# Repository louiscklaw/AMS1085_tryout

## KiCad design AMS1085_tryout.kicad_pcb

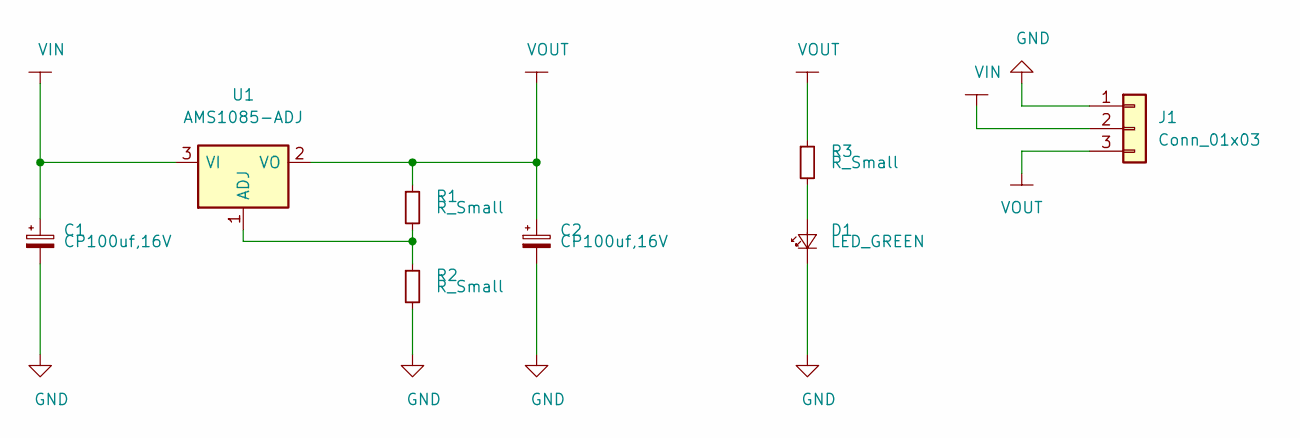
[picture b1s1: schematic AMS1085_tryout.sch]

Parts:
C1, C2: CP100uf,16V; CP_Elec_6.3x5.3
D1: LED_GREEN; LED_0805_2012Metric_Pad1.15x1.40mm_HandSolder
J1: Conn_01x03; PinHeader_1x03_P2.54mm_Vertical
R1, R2, R3: R_Small; R_1206_3216Metric_Pad1.42x1.75mm_HandSolder
U1: AMS1085-ADJ; TO-263-3_TabPin2

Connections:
GND: C1.2, C2.2, D1.1 (K), J1.1, R2.2
unnamed: D1.2 (A), R3.2
unnamed: R1.2, R2.1, U1.1 (ADJ)
VIN: C1.1, J1.2, U1.3 (VI)
VOUT: C2.1, J1.3, R1.1, R3.1, U1.2 (VO)

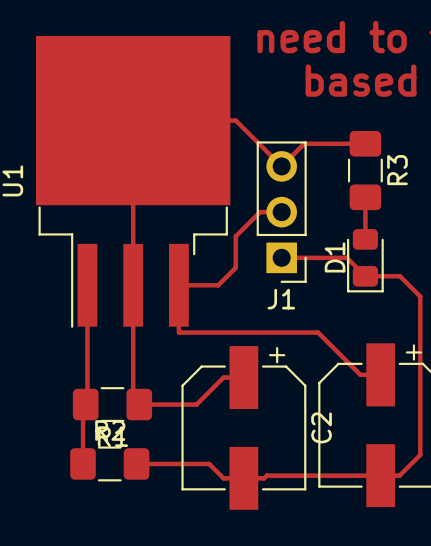
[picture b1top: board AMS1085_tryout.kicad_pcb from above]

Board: 2 copper layers, 8 parts (0 on the bottom side), 5 nets.

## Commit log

2018-12-09 update,
2020-05-05 ci: init travis build config,
2020-05-05 ci: init travis token,
